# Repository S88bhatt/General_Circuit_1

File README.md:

# General_Circuit_1
Contains all the files for General Circuit 1

## KiCad Data
Part Name is written in the reference section of each schematic symbol (Double Click in Schematic to view). Contains the footprint library and schematic symbol libraries as local libraries for ease of access.

## FreeCad Data
Contains the data generated for cutting the box plating.

## Images
Images of the physical board for reference of what the actual final product looks like.

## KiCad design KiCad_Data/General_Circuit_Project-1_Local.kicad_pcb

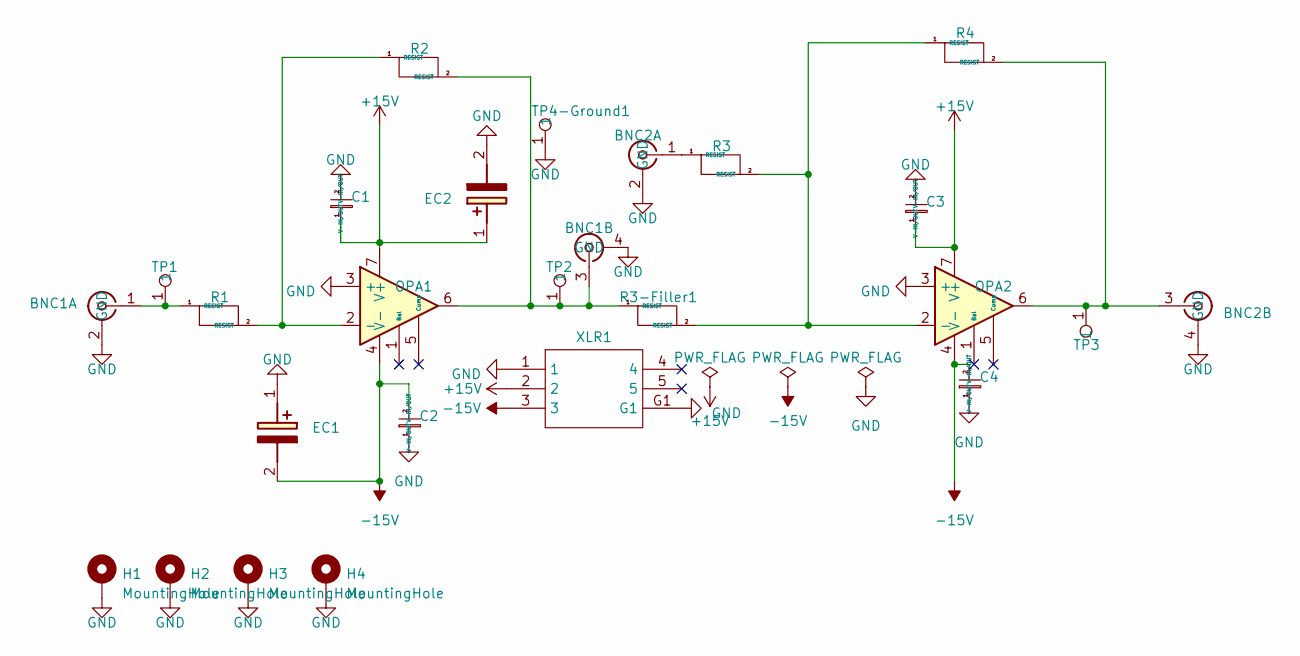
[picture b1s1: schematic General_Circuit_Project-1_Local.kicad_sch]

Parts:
BNC1, BNC2: BNC_Amphenol_031-6575_Horizontal
C1, C2, C3, C4: CAPACITOR - 399-4209-ND
EC1, EC2: EEU-EB1C102; ELECTROLYTIC CAPACITOR - EEU-EB1C102; Mouser Part Number 667-EEU-EB1C102
H1, H2, H3, H4: MountingHole; MountingHole_3.2mm_M3_DIN965_Pad
OPA1, OPA2: OPA27GP_Operational_Amplifier
R1, R2, R3, R3-Filler1, R4: R_Axial_DIN0207_L6.3mm_D2.5mm_P10.16mm_Horizontal
TP1, TP2, TP3, TP4-Ground1: TestPoint
XLR1: NC3MBH_XLR

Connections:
+15V: C1.1 (V-IN/OUT), C3.1 (V-IN/OUT), EC2.1 (+), OPA1.7 (V+), OPA2.7 (V+), XLR1.2
-15V: C2.2 (V-IN/OUT), C4.2 (V-IN/OUT), EC1.2 (-), OPA1.4 (V-), OPA2.4 (V-), XLR1.3
GND: BNC1.2 (GND), BNC1.4 (GND), BNC2.2 (GND), BNC2.4 (GND), C1.2 (V-IN/OUT), C2.1 (V-IN/OUT), C3.2 (V-IN/OUT), C4.1 (V-IN/OUT), EC1.1 (+), EC2.2 (-), H1.1, H2.1, H3.1, H4.1, OPA1.3 (+), OPA2.3 (+), TP4-Ground1.1, XLR1.1, XLR1.G1
unnamed: BNC1.1, R1.1 (RESIST), TP1.1
unnamed: BNC1.3, OPA1.6, R2.2 (RESIST), R3-Filler1.1 (RESIST), TP2.1
unnamed: BNC2.1, R3.1 (RESIST)
unnamed: BNC2.3, OPA2.6, R4.2 (RESIST), TP3.1
unnamed: OPA1.2 (-), R1.2 (RESIST), R2.1 (RESIST)
unnamed: OPA2.2 (-), R3.2 (RESIST), R3-Filler1.2 (RESIST), R4.1 (RESIST)

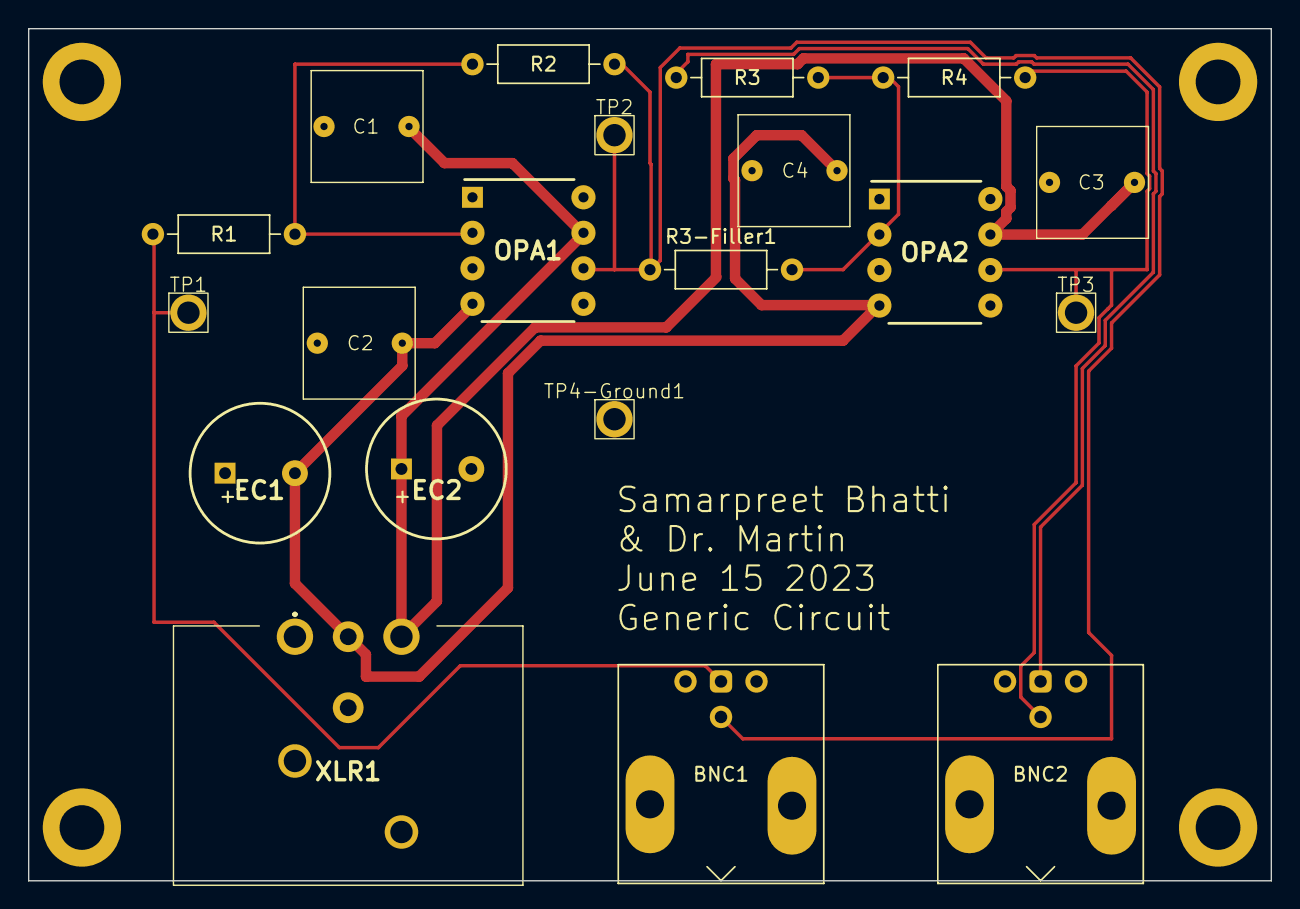
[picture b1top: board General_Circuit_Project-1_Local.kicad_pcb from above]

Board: 2 copper layers, 88.9 x 61.0 mm, 24 parts (0 on the bottom side), 9 nets.

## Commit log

2023-06-29 Create KiCad Circuit
2023-06-29 Create Data sheet
2023-06-29 Rename General_Circuit_Project-1_Local.kicad_prl to KiCad_Data/General_Circuit_Project-1_Local.kicad_prl
2023-06-29 Rename General_Circuit_Project-1_Local.kicad_pro to KiCad_Data/General_Circuit_Project-1_Local.kicad_pro
2023-06-29 Rename General_Circuit_Project-1_Local.kicad_sch to KiCad_Data/General_Circuit_Project-1_Local.kicad_sch
2023-06-29 Update and rename fp-info-cache to KiCad_Data/fp-info-cache
2023-06-29 Update and rename sym-lib-table to KiCad_Data/sym-lib-table
2023-06-29 Update and rename fp-lib-table to KiCad_Data/fp-lib-table
2023-06-29 Create Plate_Cut_Out_Prototype
2023-06-29 Create READ
2023-07-05 Jims changes
2023-07-27 Added Images to file
2023-07-27 Changed Image names
2023-07-27 Update Readme, added more details
